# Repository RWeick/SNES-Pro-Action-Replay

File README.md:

# SNES-Pro-Action-Replay
Everything necessary to produce the SNES Pro Action Replay

PCB Thickness: 1.2 mm

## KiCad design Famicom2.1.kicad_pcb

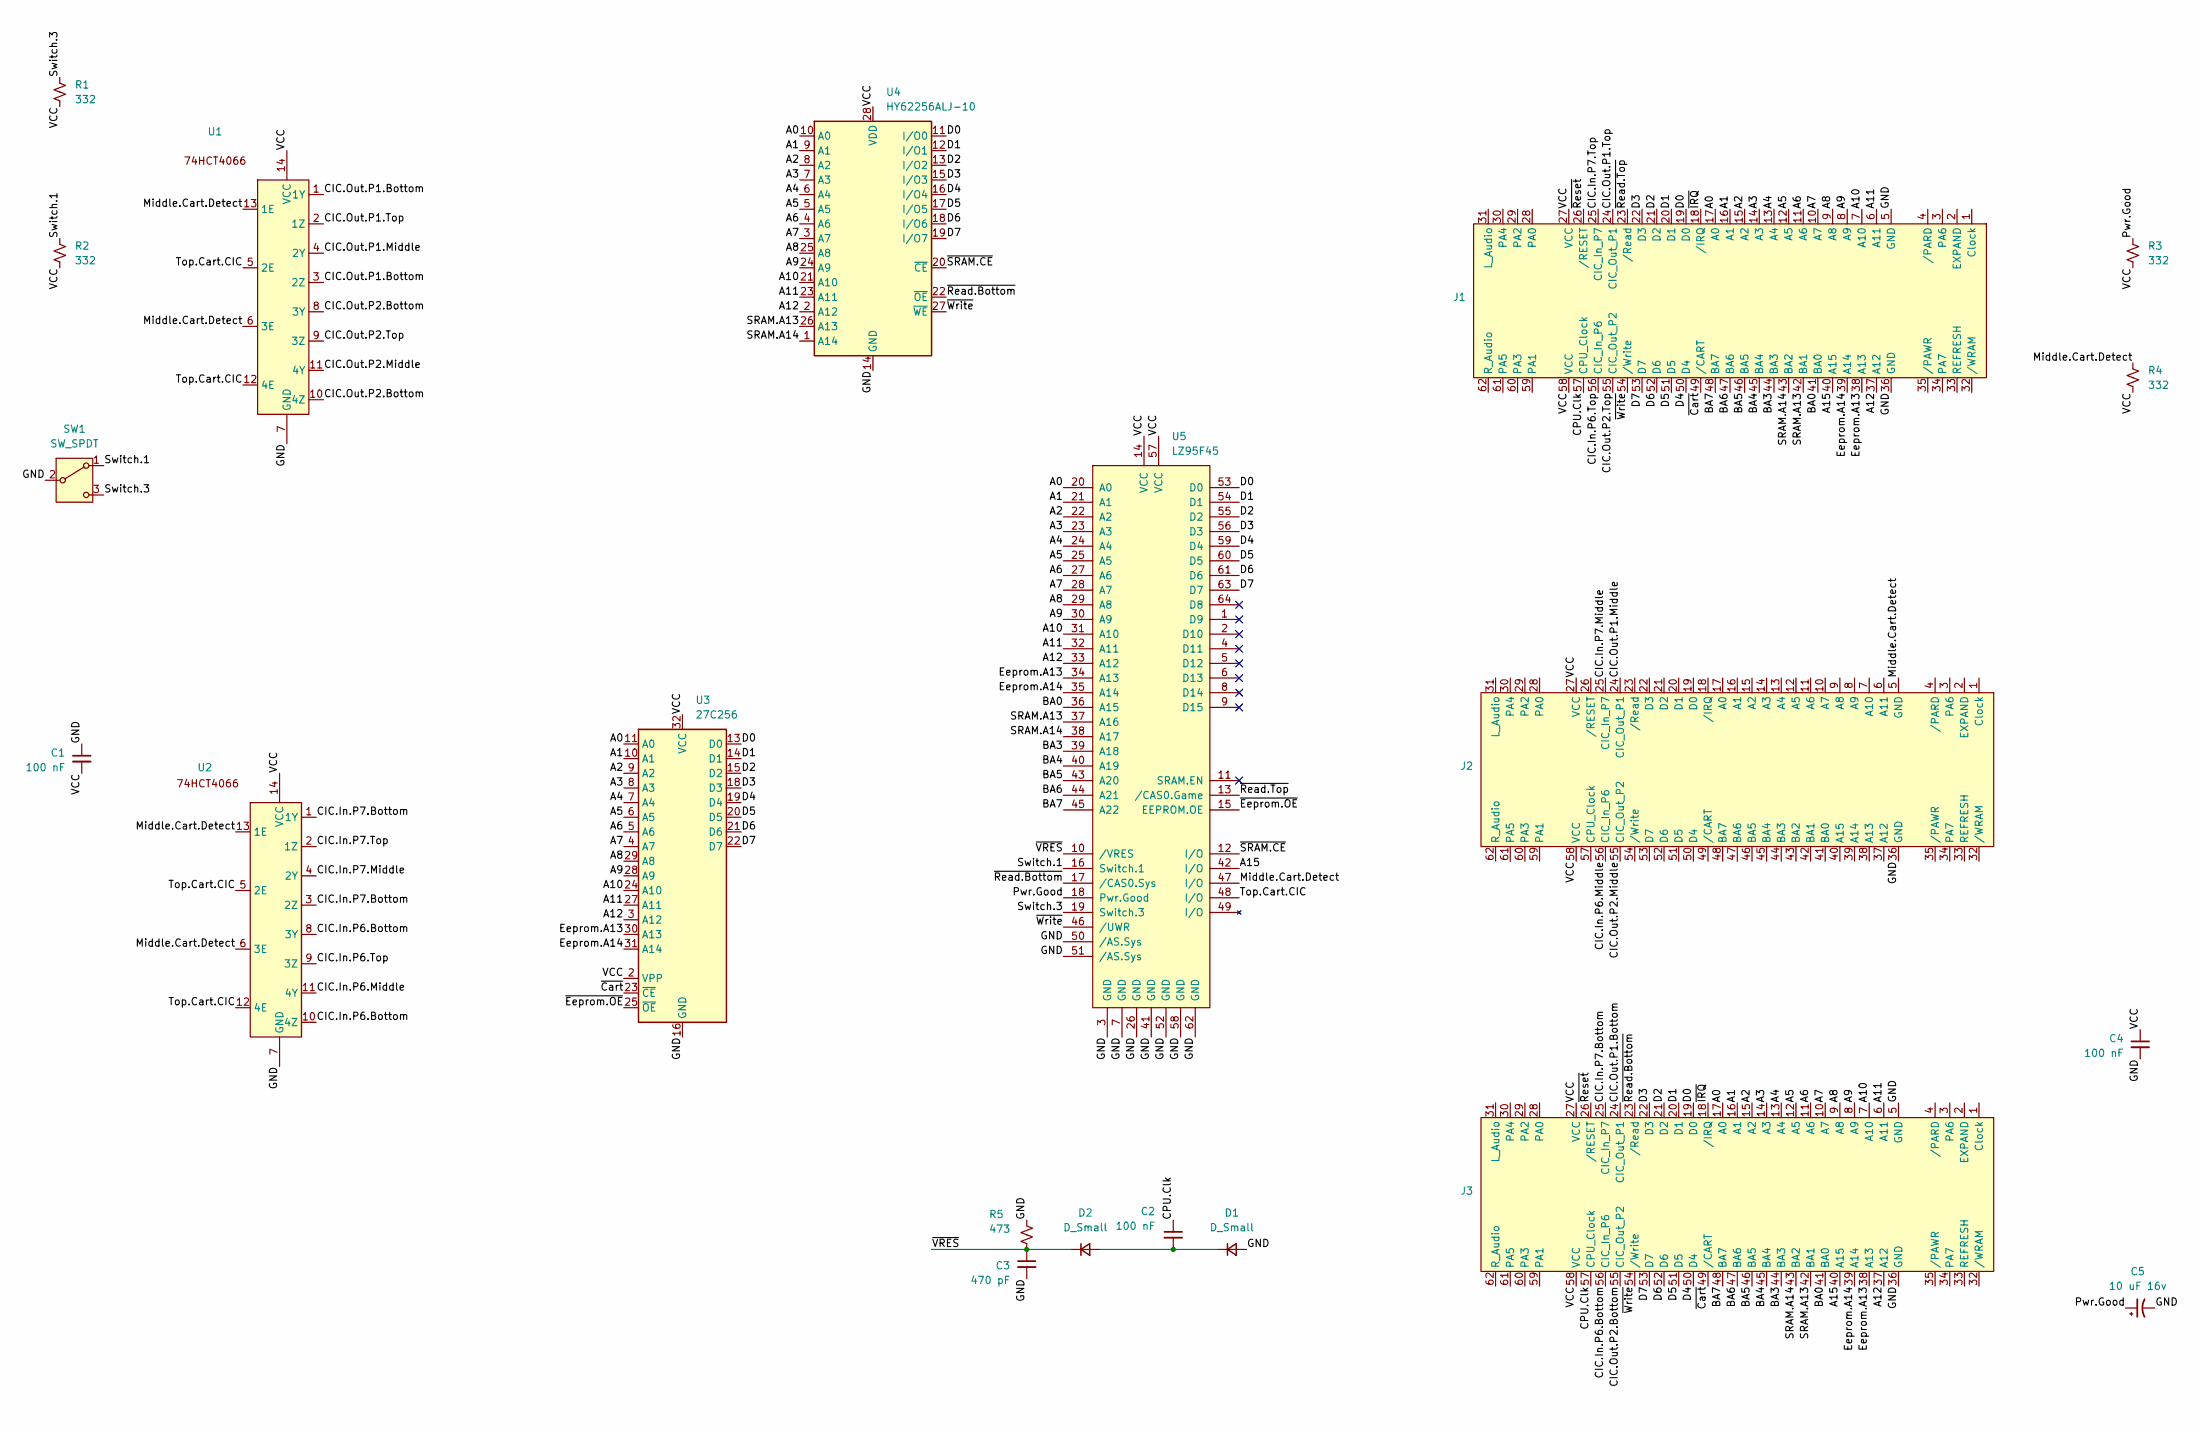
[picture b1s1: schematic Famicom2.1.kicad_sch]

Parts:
C1, C2, C4: 100 nF; Passive SMD
C3: 470 pF; Passive SMD
C5: 10 uF 16v; THT Capacitor
D1, D2: D_Small; Passive SMD
J1, J3: Edge Connector
J2: THT Cartridge Connector
R1, R2, R3, R4: 332; Passive SMD
R5: 473; Passive SMD
SW1: SW_SPDT; Switch
U1, U2: 74HCT4066
U3: 27C256
U4: HY62256ALJ-10
U5: LZ95F45

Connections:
/A0: J1.17 (A0), J3.17 (A0), U3.11 (A0), U4.10 (A0), U5.20 (A0)
/A1: J1.16 (A1), J3.16 (A1), U3.10 (A1), U4.9 (A1), U5.21 (A1)
/A2: J1.15 (A2), J3.15 (A2), U3.9 (A2), U4.8 (A2), U5.22 (A2)
/A3: J1.14 (A3), J3.14 (A3), U3.8 (A3), U4.7 (A3), U5.23 (A3)
/A4: J1.13 (A4), J3.13 (A4), U3.7 (A4), U4.6 (A4), U5.24 (A4)
/A5: J1.12 (A5), J3.12 (A5), U3.6 (A5), U4.5 (A5), U5.25 (A5)
/A6: J1.11 (A6), J3.11 (A6), U3.5 (A6), U4.4 (A6), U5.27 (A6)
/A7: J1.10 (A7), J3.10 (A7), U3.4 (A7), U4.3 (A7), U5.28 (A7)
/A8: J1.9 (A8), J3.9 (A8), U3.29 (A8), U4.25 (A8), U5.29 (A8)
/A9: J1.8 (A9), J3.8 (A9), U3.28 (A9), U4.24 (A9), U5.30 (A9)
/A10: J1.7 (A10), J3.7 (A10), U3.24 (A10), U4.21 (A10), U5.31 (A10)
/A11: J1.6 (A11), J3.6 (A11), U3.27 (A11), U4.23 (A11), U5.32 (A11)
/A12: J1.37 (A12), J3.37 (A12), U3.3 (A12), U4.2 (A12), U5.33 (A12)
/A15: J1.40 (A15), J3.40 (A15), U5.42 (I/O)
/BA0: J1.41 (BA0), J3.41 (BA0), U5.36 (A15)
/BA3: J1.44 (BA3), J3.44 (BA3), U5.39 (A18)
/BA4: J1.45 (BA4), J3.45 (BA4), U5.40 (A19)
/BA5: J1.46 (BA5), J3.46 (BA5), U5.43 (A20)
/BA6: J1.47 (BA6), J3.47 (BA6), U5.44 (A21)
/BA7: J1.48 (BA7), J3.48 (BA7), U5.45 (A22)
/CIC.In.P6.Bottom: J3.56 (CIC_In_P6), U2.8 (3Y), U2.10 (4Z)
/CIC.In.P6.Middle: J2.56 (CIC_In_P6), U2.11 (4Y)
/CIC.In.P6.Top: J1.56 (CIC_In_P6), U2.9 (3Z)
/CIC.In.P7.Bottom: J3.25 (CIC_In_P7), U2.1 (1Y), U2.3 (2Z)
/CIC.In.P7.Middle: J2.25 (CIC_In_P7), U2.4 (2Y)
/CIC.In.P7.Top: J1.25 (CIC_In_P7), U2.2 (1Z)
/CIC.Out.P1.Bottom: J3.24 (CIC_Out_P1), U1.1 (1Y), U1.3 (2Z)
/CIC.Out.P1.Middle: J2.24 (CIC_Out_P1), U1.4 (2Y)
/CIC.Out.P1.Top: J1.24 (CIC_Out_P1), U1.2 (1Z)
/CIC.Out.P2.Bottom: J3.55 (CIC_Out_P2), U1.8 (3Y), U1.10 (4Z)
/CIC.Out.P2.Middle: J2.55 (CIC_Out_P2), U1.11 (4Y)
/CIC.Out.P2.Top: J1.55 (CIC_Out_P2), U1.9 (3Z)
/CPU.Clk: C2.1, J1.57 (CPU_Clock), J3.57 (CPU_Clock)
/D0: J1.19 (D0), J3.19 (D0), U3.13 (D0), U4.11 (I/O0), U5.53 (D0)
/D1: J1.20 (D1), J3.20 (D1), U3.14 (D1), U4.12 (I/O1), U5.54 (D1)
/D2: J1.21 (D2), J3.21 (D2), U3.15 (D2), U4.13 (I/O2), U5.55 (D2)
/D3: J1.22 (D3), J3.22 (D3), U3.18 (D3), U4.15 (I/O3), U5.56 (D3)
/D4: J1.50 (D4), J3.50 (D4), U3.19 (D4), U4.16 (I/O4), U5.59 (D4)
/D5: J1.51 (D5), J3.51 (D5), U3.20 (D5), U4.17 (I/O5), U5.60 (D5)
/D6: J1.52 (D6), J3.52 (D6), U3.21 (D6), U4.18 (I/O6), U5.61 (D6)
/D7: J1.53 (D7), J3.53 (D7), U3.22 (D7), U4.19 (I/O7), U5.63 (D7)
/Eeprom.A13: J1.38 (A13), J3.38 (A13), U3.30 (A13), U5.34 (A13)
/Eeprom.A14: J1.39 (A14), J3.39 (A14), U3.31 (A14), U5.35 (A14)
/GND: C1.1, C3.2, C4.2, C5.2, D1.2 (A), J1.5 (GND), J1.36 (GND), J2.36 (GND), J3.5 (GND), J3.36 (GND), R5.1, SW1.2 (B), U1.7 (GND), U2.7 (GND), U3.16 (GND), U4.14 (GND), U5.3 (GND), U5.7 (GND), U5.26 (GND), U5.41 (GND), U5.50 (/AS.Sys), U5.51 (/AS.Sys), U5.52 (GND), U5.58 (GND), U5.62 (GND)
/Middle.Cart.Detect: J2.5 (GND), R4.1, U1.6 (3E), U1.13 (1E), U2.6 (3E), U2.13 (1E), U5.47 (I/O)
/Pwr.Good: C5.1, R3.1, U5.18 (Pwr.Good)
/SRAM.A13: J1.42 (BA1), J3.42 (BA1), U4.26 (A13), U5.37 (A16)
/SRAM.A14: J1.43 (BA2), J3.43 (BA2), U4.1 (A14), U5.38 (A17)
/Switch.1: R2.1, SW1.1 (A), U5.16 (Switch.1)
/Switch.3: R1.1, SW1.3 (C), U5.19 (Switch.3)
/Top.Cart.CIC: U1.5 (2E), U1.12 (4E), U2.5 (2E), U2.12 (4E), U5.48 (I/O)
/VCC: C1.2, C4.1, J1.27 (VCC), J1.58 (VCC), J2.27 (VCC), J2.58 (VCC), J3.27 (VCC), J3.58 (VCC), R1.2, R2.2, R3.2, R4.2, U1.14 (VCC), U2.14 (VCC), U3.2 (VPP), U3.32 (VCC), U4.28 (VDD), U5.14 (VCC), U5.57 (VCC)
/~Cart: J1.49 (/CART), J3.49 (/CART), U3.23 (~CE)
/~Eeprom.OE: U3.25 (~OE), U5.15 (EEPROM.OE)
/~IRQ: J1.18 (/IRQ), J3.18 (/IRQ)
/~Read.Bottom: J3.23 (/Read), U4.22 (~OE), U5.17 (/CAS0.Sys)
/~Read.Top: J1.23 (/Read), U5.13 (/CAS0.Game)
/~Reset: J1.26 (/RESET), J3.26 (/RESET)
/~SRAM.CE: U4.20 (~CE), U5.12 (I/O)
/~VRES: C3.1, D2.1 (K), R5.2, U5.10 (/VRES)
/~Write: J1.54 (/Write), J3.54 (/Write), U4.27 (~WE), U5.46 (/UWR)
unnamed: C2.2, D1.1 (K), D2.2 (A)

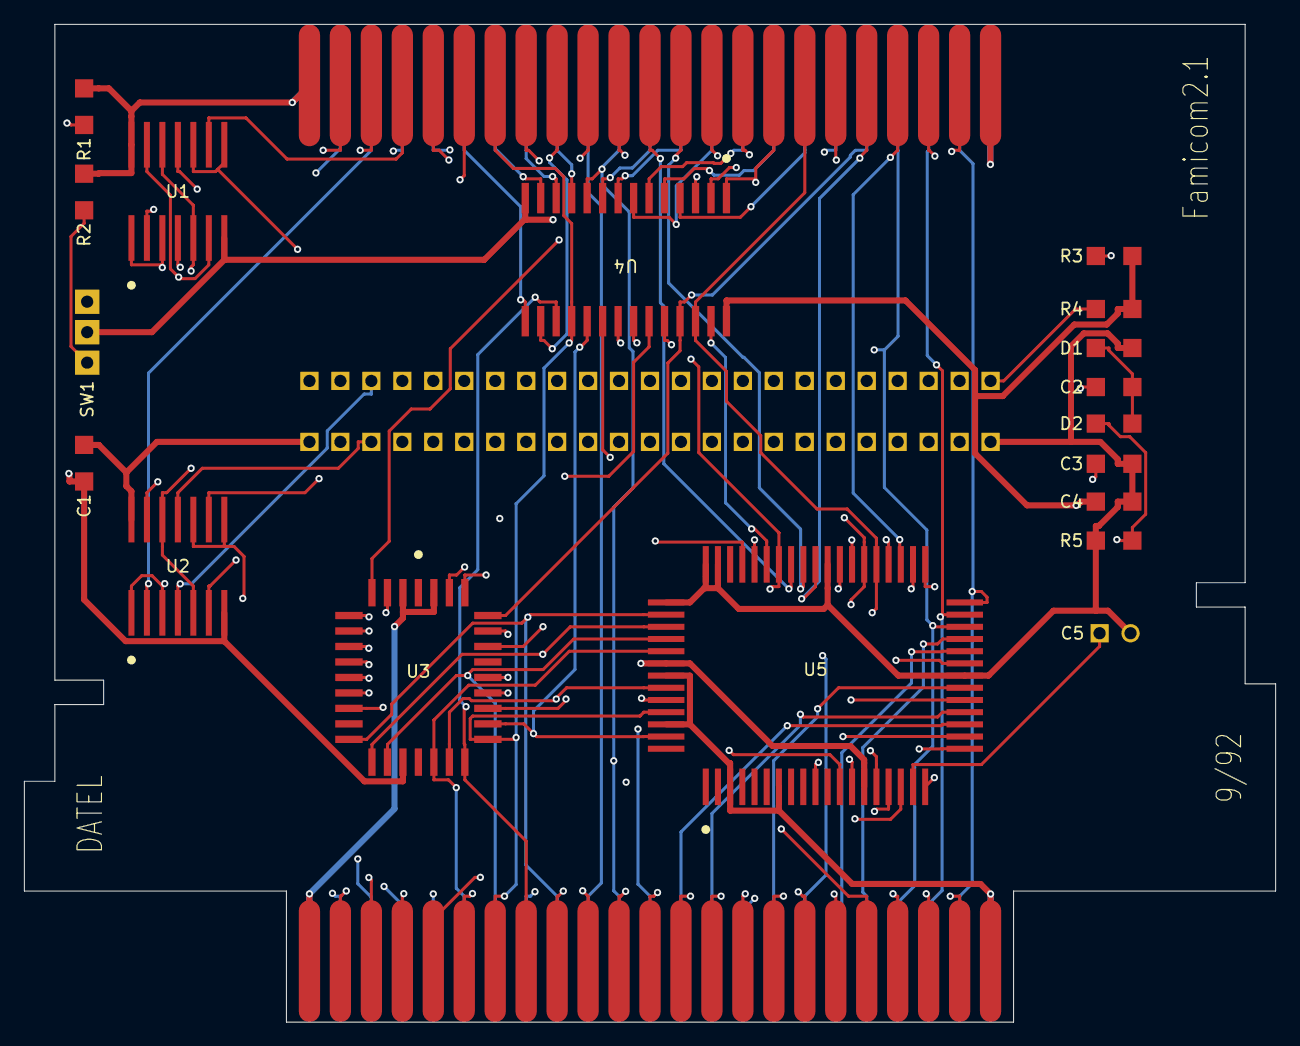
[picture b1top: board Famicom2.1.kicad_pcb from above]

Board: 4 copper layers, 102.7 x 81.8 mm, 21 parts (0 on the bottom side), 62 nets.
